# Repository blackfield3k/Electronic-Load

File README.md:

# Electronic Load
 An RP2040 controlled Mosfet Electronic Load

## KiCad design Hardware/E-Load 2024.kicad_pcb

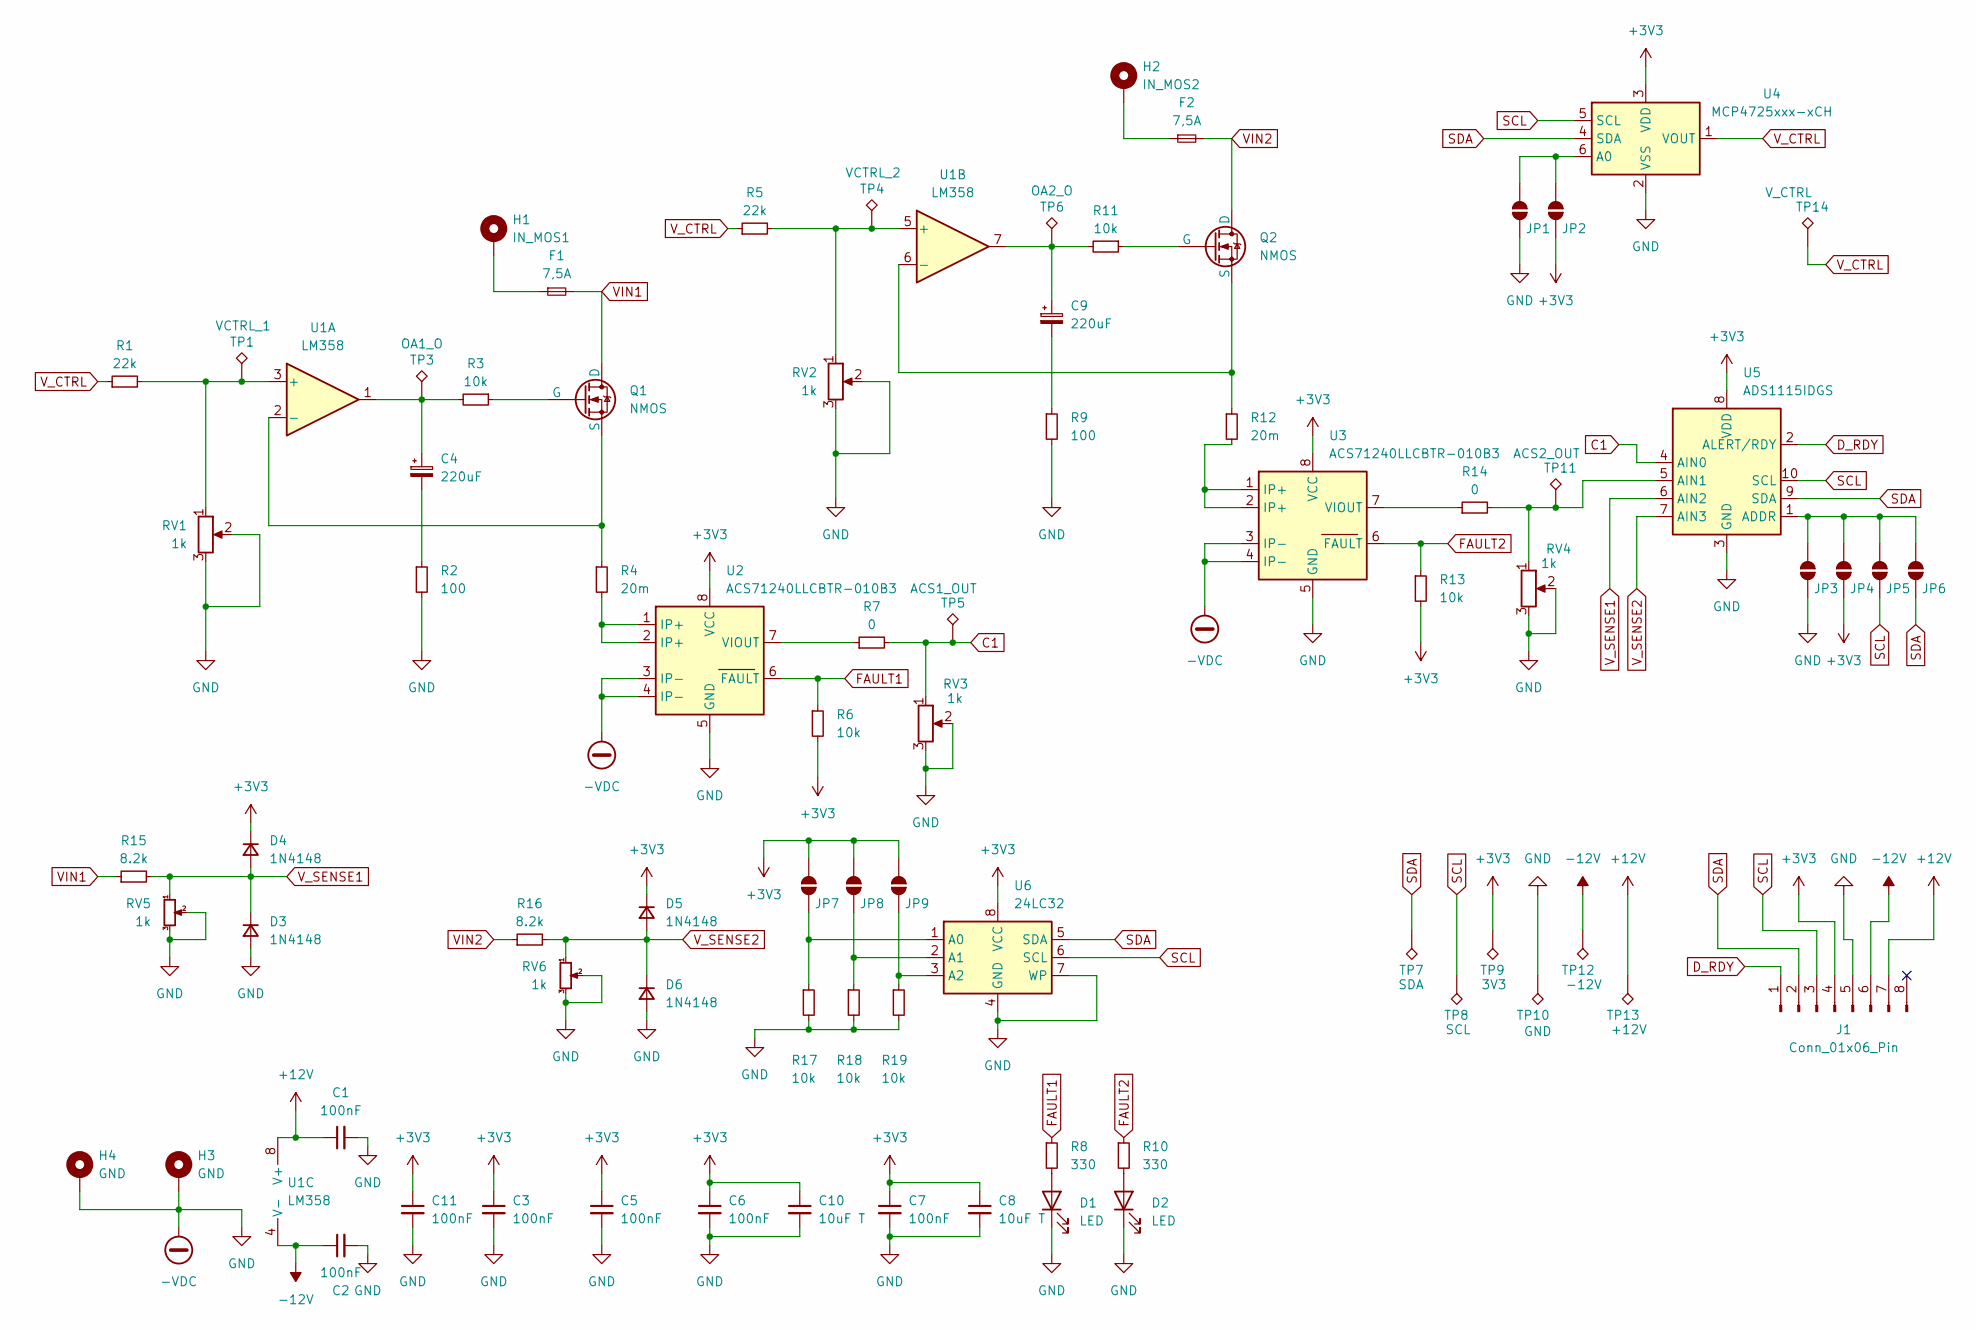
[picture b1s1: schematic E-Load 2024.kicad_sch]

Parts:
C1, C2, C3, C5, C6, C7, C11: 100nF; C_0805_2012Metric
C4, C9: 220uF; CP_Elec_6.3x5.8
C8, C10: 10uF T; C_1206_3216Metric
D1, D2: LED; LED_0805_2012Metric
D3, D4, D5, D6: 1N4148; D_SOD-323
F1, F2: 7,5A; BX503-35
H1: IN_MOS1; MountingHole_5.3mm_M5_Pad_Via
H2: IN_MOS2; MountingHole_5.3mm_M5_Pad_Via
H3, H4: GND; MountingHole_5.3mm_M5_Pad_Via
J1: Conn_01x06_Pin; JST_XH_B8B-XH-A_1x08_P2.50mm_Vertical
JP1, JP2, JP3, JP4, JP5, JP6: SolderJumper_2_Open; SolderJumper-2_P1.3mm_Open_RoundedPad1.0x1.5mm
JP7: A0; SolderJumper-2_P1.3mm_Open_RoundedPad1.0x1.5mm
JP8: A1; SolderJumper-2_P1.3mm_Open_RoundedPad1.0x1.5mm
JP9: A2; SolderJumper-2_P1.3mm_Open_RoundedPad1.0x1.5mm
Q1, Q2: NMOS; TO-247-3_Vertical
R1, R5: 22k; R_0805_2012Metric
R2, R9: 100; R_0805_2012Metric
R3, R6, R11, R13, R17, R18, R19: 10k; R_0805_2012Metric
R4, R12: 20m; R_1210_3225Metric_Pad1.30x2.65mm_HandSolder
R7, R14: 0; R_0805_2012Metric
R8, R10: 330; R_0805_2012Metric
R15, R16: 8.2k; R_0805_2012Metric
RV1, RV2, RV3, RV4, RV5, RV6: 1k; Potentiometer_Bourns_3296W_Vertical
TP1: VCTRL_1; TestPoint_Pad_D2.5mm
TP3: OA1_O; TestPoint_Pad_D2.5mm
TP4: VCTRL_2; TestPoint_Pad_D2.5mm
TP5: ACS1_OUT; TestPoint_Pad_D2.5mm
TP6: OA2_O; TestPoint_Pad_D2.5mm
TP7: SDA; TestPoint_Pad_D2.5mm
TP8: SCL; TestPoint_Pad_D2.5mm
TP9: 3V3; TestPoint_Pad_D2.5mm
TP10: GND; TestPoint_Pad_D2.5mm
TP11: ACS2_OUT; TestPoint_Pad_D2.5mm
TP12: -12V; TestPoint_Pad_D2.5mm
TP13: +12V; TestPoint_Pad_D2.5mm
TP14: V_CTRL; TestPoint_Pad_D2.5mm
U1: LM358; TSSOP-8_4.4x3mm_P0.65mm
U2, U3: ACS71240LLCBTR-010B3; SOIC-8_3.9x4.9mm_P1.27mm
U4: MCP4725xxx-xCH; SOT-23-6
U5: ADS1115IDGS; VSSOP-10_3x3mm_P0.5mm
U6: 24LC32; SOIC-8_3.9x4.9mm_P1.27mm

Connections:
+3V3: C3.1, C5.1, C6.1, C7.1, C8.1, C10.1, C11.1, D4.1 (K), D5.1 (K), J1.4, JP2.1 (A), JP4.1 (A), JP7.2 (B), JP8.2 (B), JP9.2 (B), R6.2, R13.2, TP9.1, U2.8 (VCC), U3.8 (VCC), U4.3 (VDD), U5.8 (VDD), U6.8 (VCC)
+12V: C1.1, J1.7, TP13.1, U1.8 (V+)
-12V: C2.1, J1.6, TP12.1, U1.4 (V-)
-VDC: C1.2, C2.2, C3.2, C5.2, C6.2, C7.2, C8.2, C10.2, C11.2, D1.1 (K), D2.1 (K), D3.2 (A), D6.2 (A), H3.1, H4.1, J1.5, JP1.1 (A), JP3.1 (A), R2.2, R9.2, R17.2, R18.2, R19.2, RV1.2, RV1.3, RV2.2, RV2.3, RV3.2, RV3.3, RV4.2, RV4.3, RV5.2, RV5.3, RV6.2, RV6.3, TP10.1, U2.3 (IP-), U2.4 (IP-), U2.5 (GND), U3.3 (IP-), U3.4 (IP-), U3.5 (GND), U4.2 (VSS), U5.3 (GND), U6.4 (GND), U6.7 (WP)
C1: R7.2, RV3.1, TP5.1, U5.4 (AIN0)
D_RDY: J1.1, U5.2 (ALERT/RDY)
FAULT1: R6.1, R8.1, U2.6 (FAULT)
FAULT2: R10.1, R13.1, U3.6 (FAULT)
unnamed: C4.1, R3.2, TP3.1, U1.1
unnamed: C4.2, R2.1
unnamed: C9.1, R11.2, TP6.1, U1.7
unnamed: C9.2, R9.1
unnamed: D1.2 (A), R8.2
unnamed: D2.2 (A), R10.2
unnamed: F1.1, H1.1
unnamed: F2.1, H2.1
unnamed: JP1.2 (B), JP2.2 (B), U4.6 (A0)
unnamed: JP3.2 (B), JP4.2 (B), JP5.2 (B), JP6.2 (B), U5.1 (ADDR)
unnamed: JP7.1 (A), R17.1, U6.1 (A0)
unnamed: JP8.1 (A), R18.1, U6.2 (A1)
unnamed: JP9.1 (A), R19.1, U6.3 (A2)
unnamed: Q1.2 (G), R3.1
unnamed: Q1.3 (S), R4.1, U1.2 (-)
unnamed: Q2.2 (G), R11.1
unnamed: Q2.3 (S), R12.1, U1.6 (-)
unnamed: R4.2, U2.1 (IP+), U2.2 (IP+)
unnamed: R12.2, U3.1 (IP+), U3.2 (IP+)
unnamed: R1.2, RV1.1, TP1.1, U1.3 (+)
unnamed: R5.2, RV2.1, TP4.1, U1.5 (+)
unnamed: R7.1, U2.7 (VIOUT)
unnamed: R14.1, U3.7 (VIOUT)
unnamed: R14.2, RV4.1, TP11.1, U5.5 (AIN1)
SCL: J1.3, JP5.1 (A), TP8.1, U4.5 (SCL), U5.10 (SCL), U6.6 (SCL)
SDA: J1.2, JP6.1 (A), TP7.1, U4.4 (SDA), U5.9 (SDA), U6.5 (SDA)
VIN1: F1.2, Q1.1 (D), R15.1
VIN2: F2.2, Q2.1 (D), R16.1
V_CTRL: R1.1, R5.1, TP14.1, U4.1 (VOUT)
V_SENSE1: D3.1 (K), D4.2 (A), R15.2, RV5.1, U5.6 (AIN2)
V_SENSE2: D5.2 (A), D6.1 (K), R16.2, RV6.1, U5.7 (AIN3)

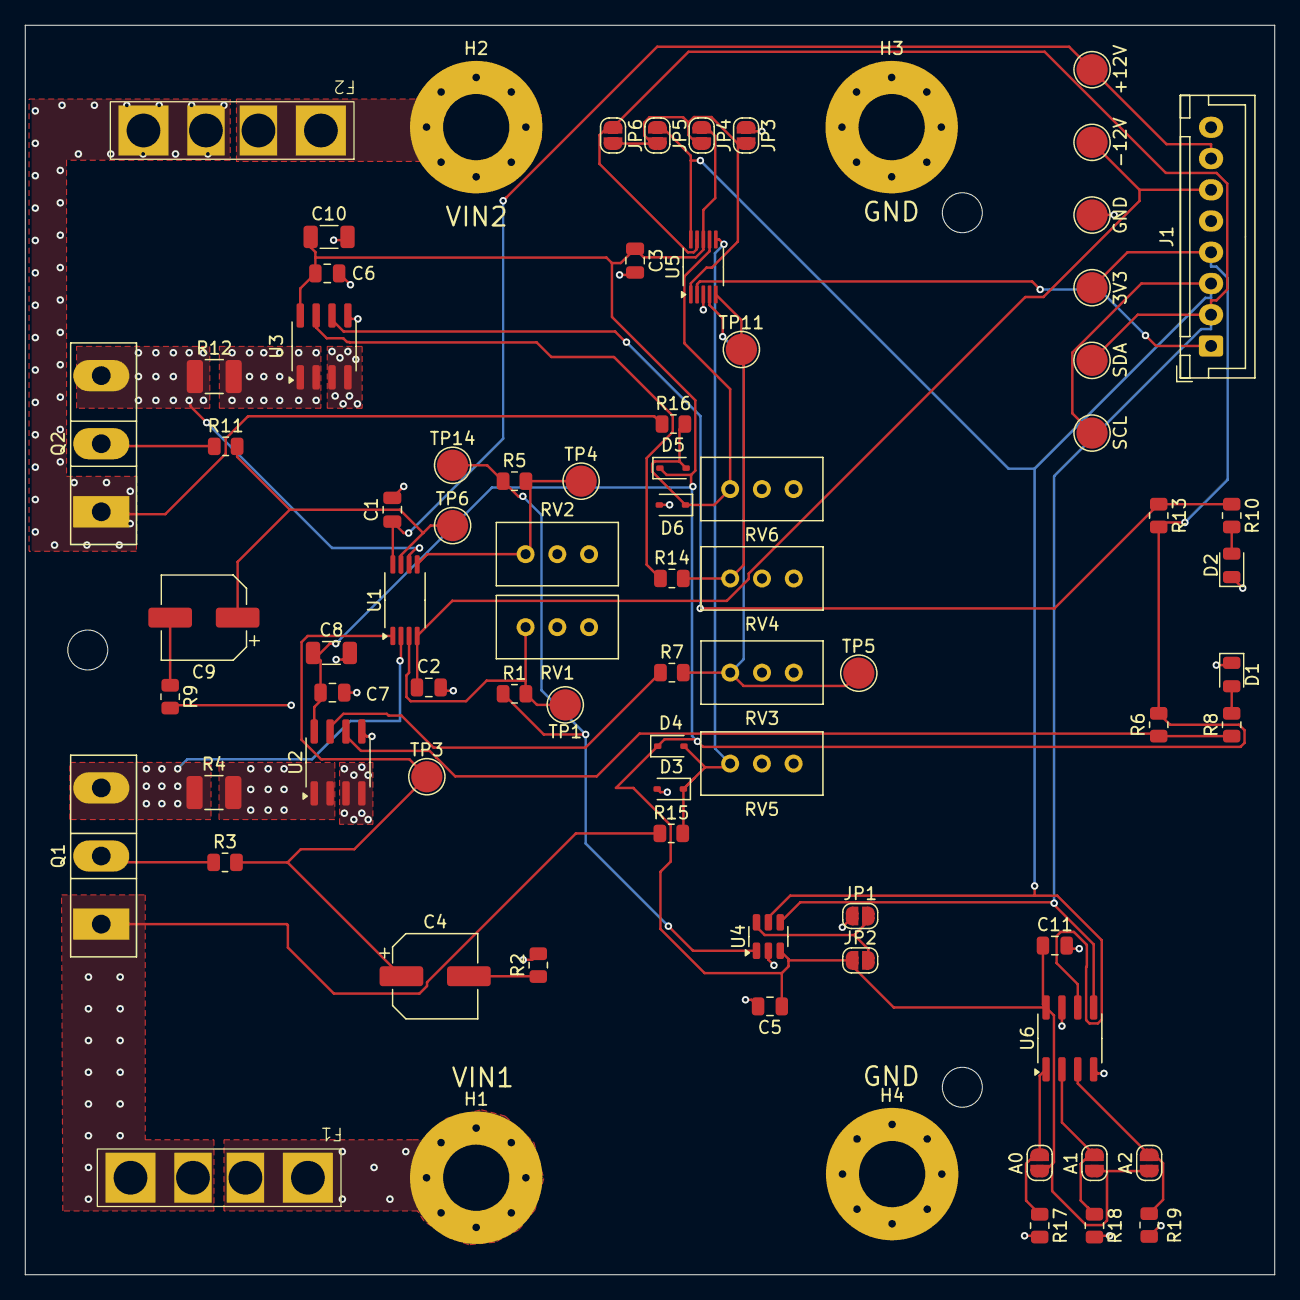
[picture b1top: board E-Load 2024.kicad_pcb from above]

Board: 2 copper layers, 100.0 x 100.0 mm, 82 parts (0 on the bottom side), 39 nets.

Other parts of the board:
M3_1, M3_2, M3_3: MountingHole_3.2mm_M3_DIN965

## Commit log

2024-05-26 Upload KiCad Project
2024-05-26 Load PCB is missing 3V3
2024-05-27 Final Version 1.0
